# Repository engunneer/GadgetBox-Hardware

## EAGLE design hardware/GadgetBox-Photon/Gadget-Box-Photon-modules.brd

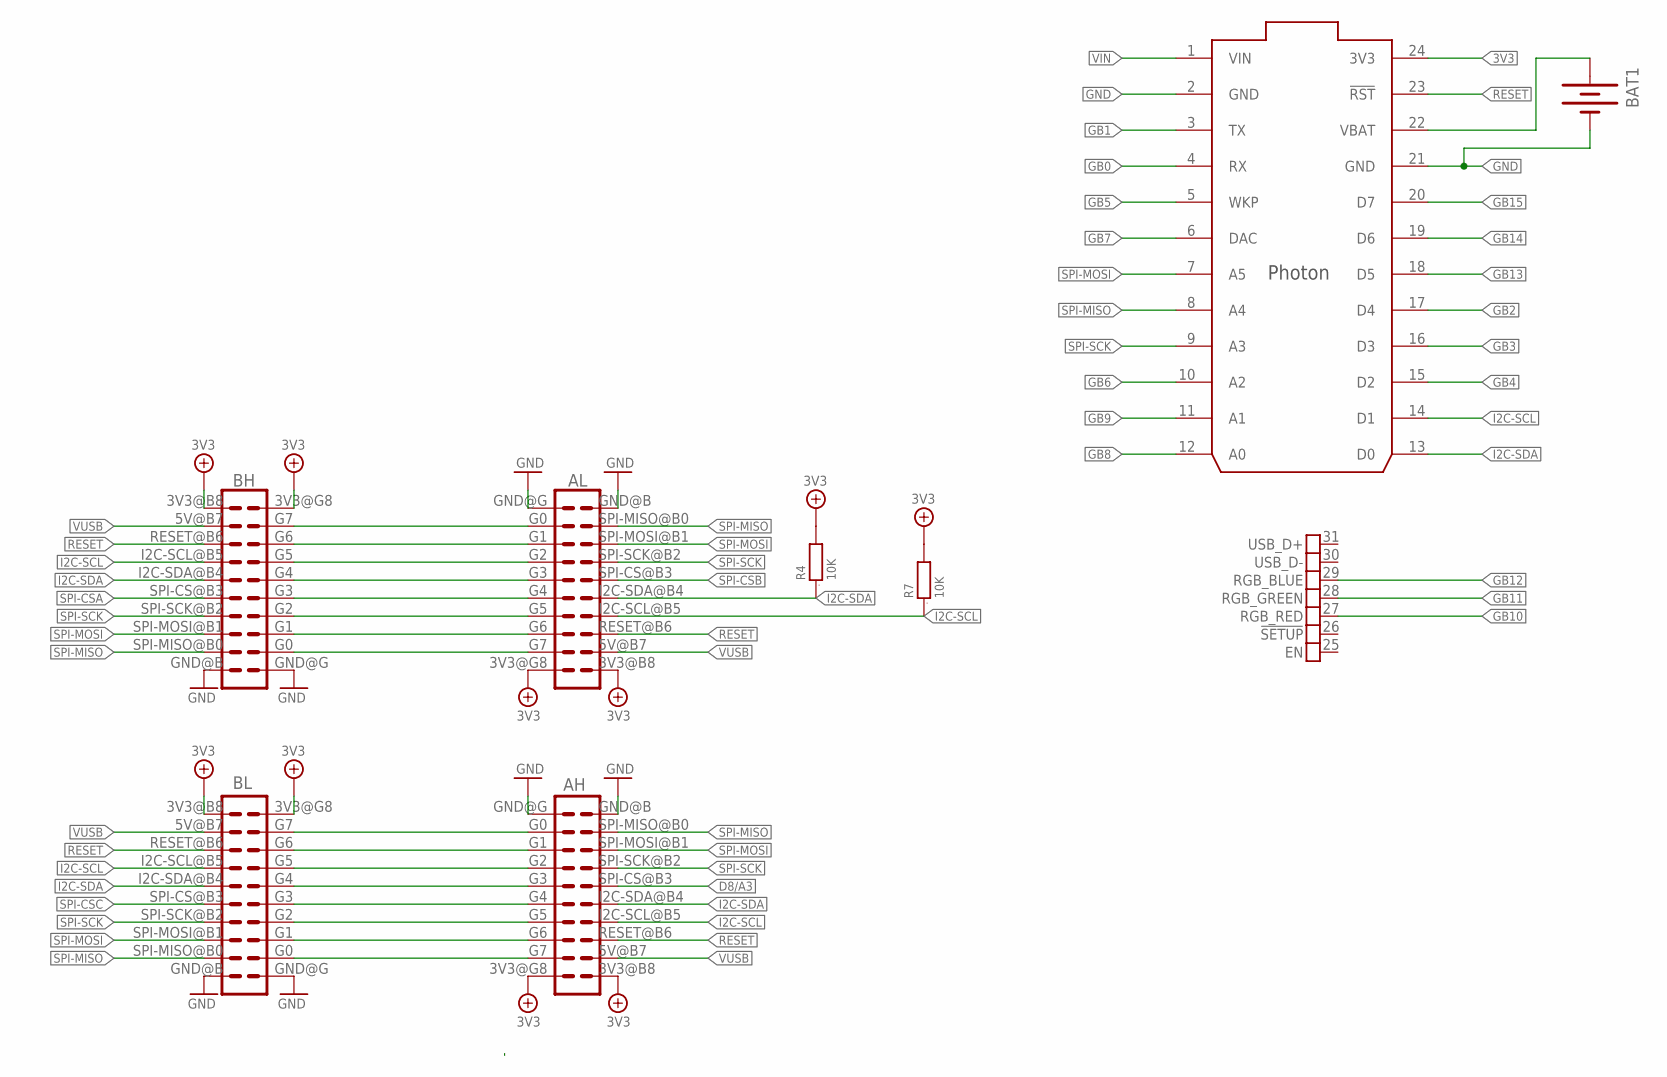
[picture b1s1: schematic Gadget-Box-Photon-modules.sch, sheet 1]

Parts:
AH: ECOGECOG_SLOT_ALT1; ECOG_ALT1; PARTNO PPPC102LFBN-RC,SULLINS CONNECTOR SOLUTI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
AL: ECOGECOG_SLOT_ALT1; ECOG_ALT1; PARTNO PPPC102LFBN-RC,SULLINS CONNECTOR SOLUTI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
BAT1: BATTERY12MM; BATTCON_12MM
BH: ECOGECOG_SLOT_ALT1; ECOG_ALT1; PARTNO PPPC102LFBN-RC,SULLINS CONNECTOR SOLUTI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
BL: ECOGECOG_SLOT_ALT1; ECOG_ALT1; PARTNO PPPC102LFBN-RC,SULLINS CONNECTOR SOLUTI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
R4, R7: 10K; 0603; PARTNO RC0603JR-0710KL,YAGEO (VA),dk,311-10KGR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
U$7: PHOTON_SMD

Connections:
3V3: AH.3V3@B8 (3V3), AH.3V3@G8 (3V3), AL.3V3@B8 (3V3), AL.3V3@G8 (3V3), BH.3V3@B8 (3V3), BH.3V3@G8 (3V3), BL.3V3@B8 (3V3), BL.3V3@G8 (3V3), R4.2, R7.2, U$7.24 (3V3)
D8/A3: AH.SPI-CS@B3 (SPI-CS)
GB0: AL.G0, BH.G7, U$7.4 (RX)
GB1: AL.G1, BH.G6, U$7.3 (TX)
GB2: AL.G2, BH.G5, U$7.17 (D4)
GB3: AL.G3, BH.G4, U$7.16 (D3)
GB4: AL.G4, BH.G3, U$7.15 (D2)
GB5: AL.G5, BH.G2, U$7.5 (WKP)
GB6: AL.G6, BH.G1, U$7.10 (A2)
GB7: AL.G7, BH.G0, U$7.6 (DAC)
GB8: AH.G0, BL.G7, U$7.12 (A0)
GB9: AH.G1, BL.G6, U$7.11 (A1)
GB10: AH.G2, BL.G5, U$7.27 (RGB_RED)
GB11: AH.G3, BL.G4, U$7.28 (RGB_GREEN)
GB12: AH.G4, BL.G3, U$7.29 (RGB_BLUE)
GB13: AH.G5, BL.G2, U$7.18 (D5)
GB14: AH.G6, BL.G1, U$7.19 (D6)
GB15: AH.G7, BL.G0, U$7.20 (D7)
GND: AH.GND@B (GND), AH.GND@G (GND), AL.GND@B (GND), AL.GND@G (GND), BAT1.GND (-), BH.GND@B (GND), BH.GND@G (GND), BL.GND@B (GND), BL.GND@G (GND), U$7.2 (GND), U$7.21 (GND); also elsewhere on the board
I2C-SCL: AH.I2C-SCL@B5 (I2C-SCL), AL.I2C-SCL@B5 (I2C-SCL), BH.I2C-SCL@B5 (I2C-SCL), BL.I2C-SCL@B5 (I2C-SCL), R7.1, U$7.14 (D1)
I2C-SDA: AH.I2C-SDA@B4 (I2C-SDA), AL.I2C-SDA@B4 (I2C-SDA), BH.I2C-SDA@B4 (I2C-SDA), BL.I2C-SDA@B4 (I2C-SDA), R4.1, U$7.13 (D0)
unnamed: BAT1.PWR@1 (+), U$7.22 (VBAT)
RESET: AH.RESET@B6 (RESET), AL.RESET@B6 (RESET), BH.RESET@B6 (RESET), BL.RESET@B6 (RESET), U$7.23 (!RST)
SPI-CSA: BH.SPI-CS@B3 (SPI-CS)
SPI-CSB: AL.SPI-CS@B3 (SPI-CS)
SPI-CSC: BL.SPI-CS@B3 (SPI-CS)
SPI-MISO: AH.SPI-MISO@B0 (SPI-MISO), AL.SPI-MISO@B0 (SPI-MISO), BH.SPI-MISO@B0 (SPI-MISO), BL.SPI-MISO@B0 (SPI-MISO), U$7.8 (A4)
SPI-MOSI: AH.SPI-MOSI@B1 (SPI-MOSI), AL.SPI-MOSI@B1 (SPI-MOSI), BH.SPI-MOSI@B1 (SPI-MOSI), BL.SPI-MOSI@B1 (SPI-MOSI), U$7.7 (A5)
SPI-SCK: AH.SPI-SCK@B2 (SPI-SCK), AL.SPI-SCK@B2 (SPI-SCK), BH.SPI-SCK@B2 (SPI-SCK), BL.SPI-SCK@B2 (SPI-SCK), U$7.9 (A3)
VIN: U$7.1 (VIN); also elsewhere on the board
VUSB: AH.5V@B7 (5V), AL.5V@B7 (5V), BH.5V@B7 (5V), BL.5V@B7 (5V); also elsewhere on the board

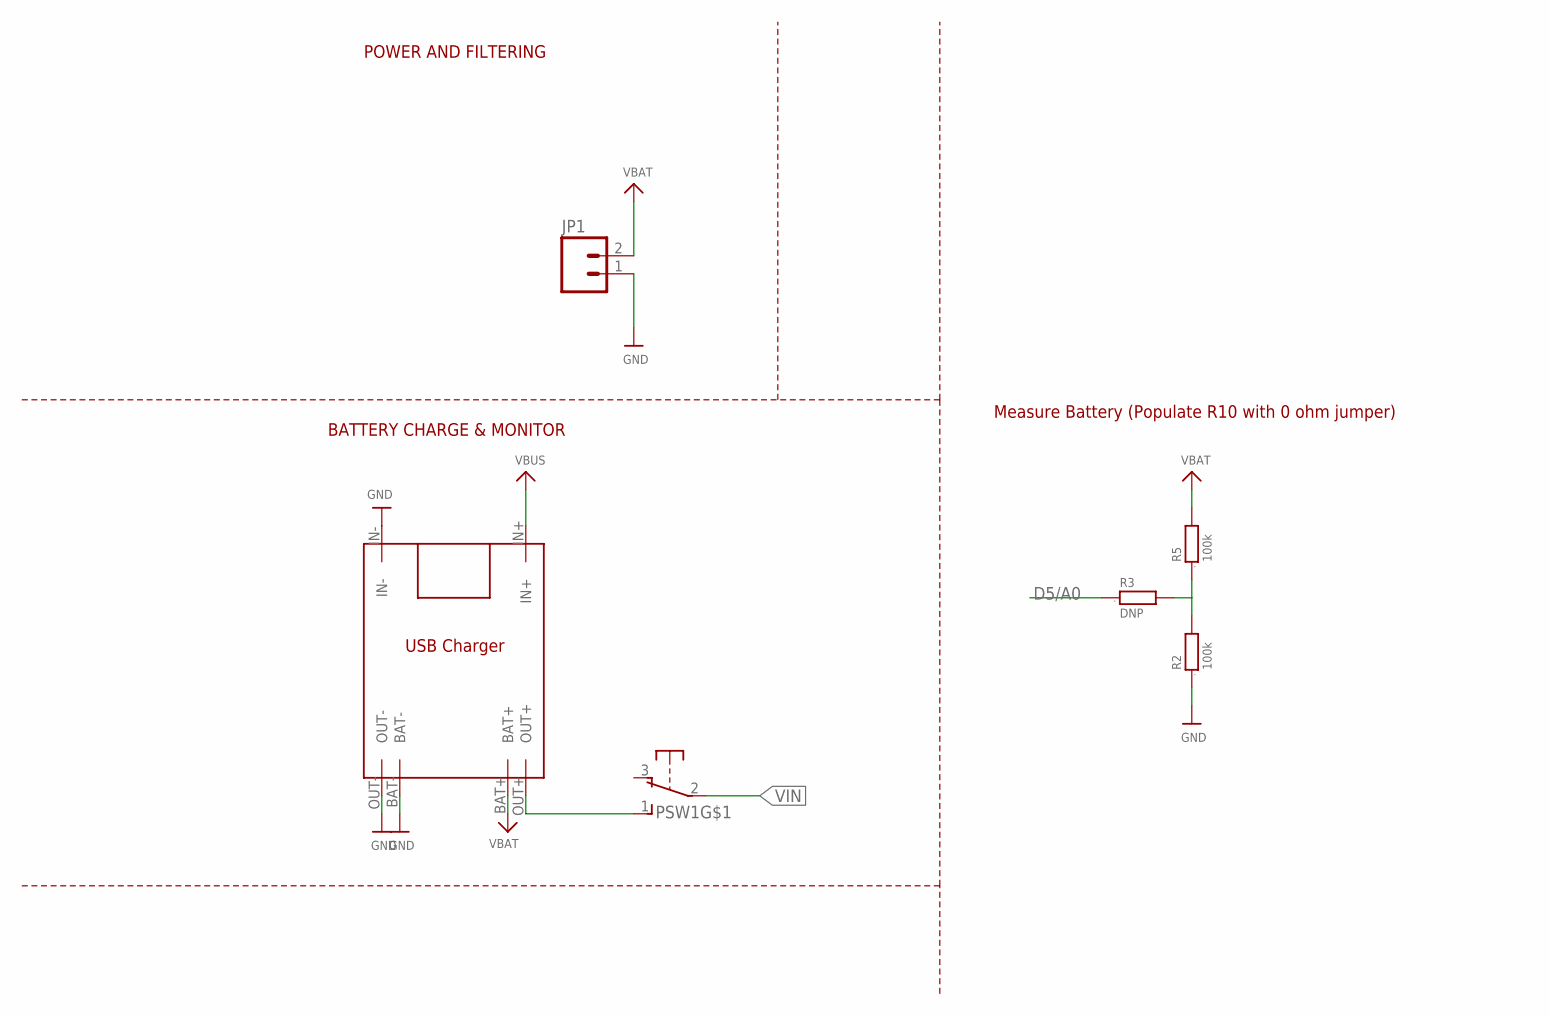
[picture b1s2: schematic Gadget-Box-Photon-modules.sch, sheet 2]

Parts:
JP1: M02-JST-2-PTH-NO_SILK; JST-2-PTH-NS; PARTNO B2B-PH-SM4-TB(LF)(SN),JST SALES AMERICA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
PSW1: OS102011MA1Q; PARTNO OS102011MA1QN1,C&K Components,dk,CKN955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
R2, R5: 100k; 0603; PARTNO RC0603JR-07100KL,YAGEO (VA),dk,311-100K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
R3: DNP; 0603
U$1: TP4056

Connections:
D5/A0: R3.1
GND: JP1.1, R2.1, U$1.BAT-, U$1.IN-, U$1.OUT-; also elsewhere on the board
unnamed: R2.2, R3.2, R5.1
VBATTTERY: JP1.2, R5.2, U$1.BAT+
VIN: PSW1.2; also elsewhere on the board
VOUT: PSW1.1 (S), U$1.OUT+
VUSB: U$1.IN+; also elsewhere on the board

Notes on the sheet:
POWER AND FILTERING
BATTERY CHARGE & MONITOR
Measure Battery (Populate R10 with 0 ohm jumper)

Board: 2 copper layers, 16 parts (1 on the bottom side), 30 nets, no tracks yet.

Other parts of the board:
$$U$1: ECOG93P53P5
U$100: GADGETBOX_TEXT

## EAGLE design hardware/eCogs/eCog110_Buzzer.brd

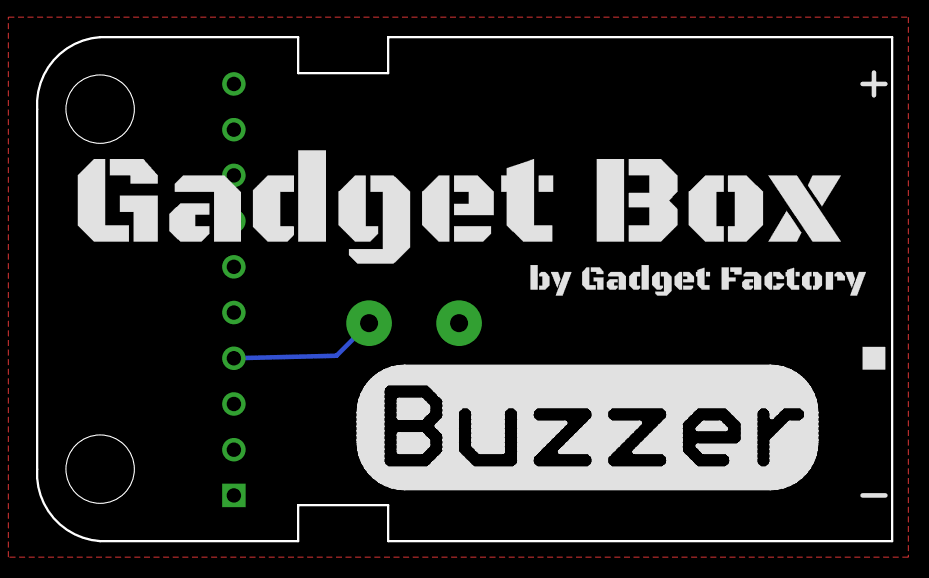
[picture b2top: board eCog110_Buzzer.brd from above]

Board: 2 copper layers, 47.5 x 28.0 mm, 4 parts (1 on the bottom side), 2 nets.

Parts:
ECOG: ECOG_GENERAL_ROWTHROUGHOLE; ECOG_GENERAL_TH
SP1: SPEAKER/PS12; PS12
U$1: GADGETBOX_TEXT
U$4: LEGEND_PWM

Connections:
GND: ECOG.GND, SP1.P$1
unnamed: ECOG.G2, SP1.P$2

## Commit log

2016-12-12 iniitial
2016-12-13 photon IO selected
    still need CS for SPI ports

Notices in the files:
hardware/GadgetBox-Photon/Gadget-Box-Photon-modules.brd:
Copyright 2016
parts and their libraries:
SparkFun: Licensing: CC v3.0 Share-Alike You are welcome to use this library for commercial purposes.
SparkFun-Electromechanical: Licensing: Creative Commons ShareAlike 4.0 International - https://creativecommons.org/licenses/by-sa/4.0
